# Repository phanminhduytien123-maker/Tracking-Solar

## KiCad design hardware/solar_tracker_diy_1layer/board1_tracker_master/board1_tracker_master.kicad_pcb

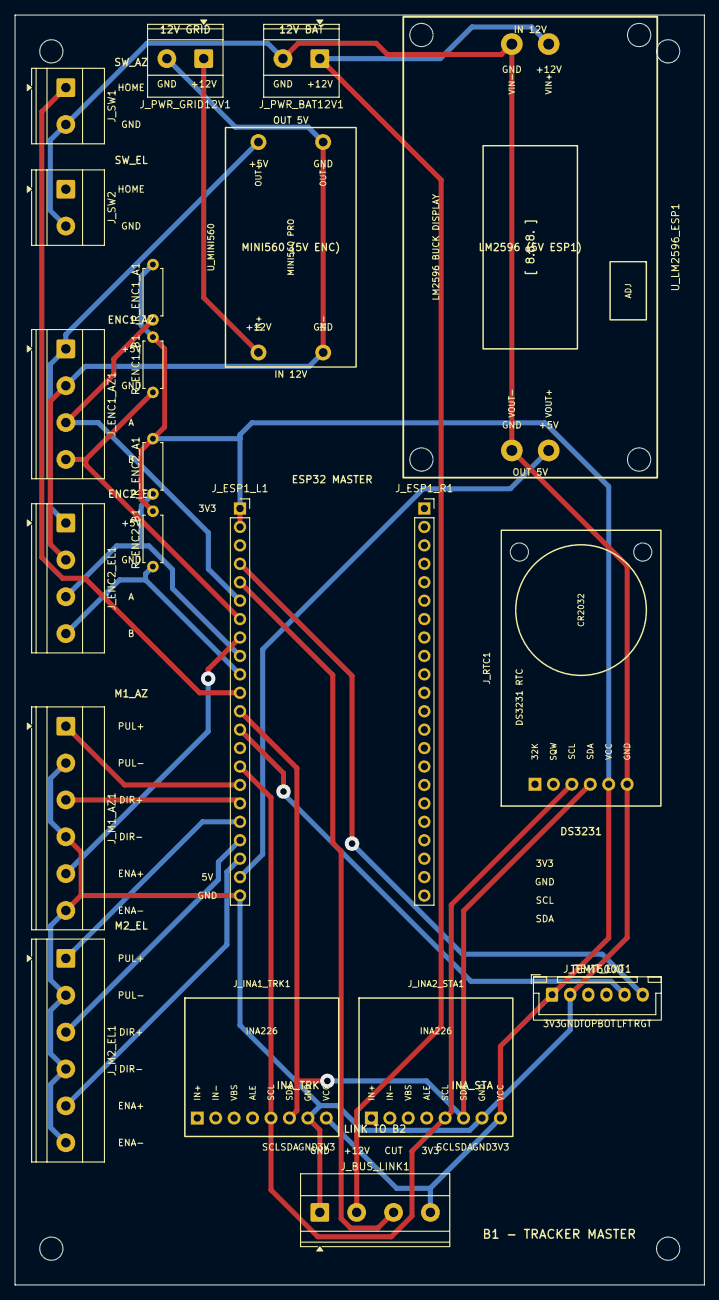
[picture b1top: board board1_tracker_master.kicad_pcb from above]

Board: 2 copper layers, 95.0 x 175.0 mm, 21 parts (0 on the bottom side), 23 nets.

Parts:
J_BUS_LINK1: Bus Lien Bo; TerminalBlock_Phoenix_MKDS-1,5-4-5.08_1x04_P5.08mm_Horizont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
J_ENC1_AZ1: Encoder 1 Az; TerminalBlock_Phoenix_MKDS-1,5-4-5.08_1x04_P5.08mm_Horizont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
J_ENC2_EL1: Encoder 2 El; TerminalBlock_Phoenix_MKDS-1,5-4-5.08_1x04_P5.08mm_Horizont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
J_ESP1_L1: ESP1 J1 Left; PinSocket_1x22_P2.54mm_Vertical
J_ESP1_R1: ESP1 J3 Right; PinSocket_1x22_P2.54mm_Vertical
J_INA1_TRK1: INA226 Trk; INA226_CJMCU226_Module
J_INA2_STA1: INA226 Sta; INA226_CJMCU226_Module
J_M1_AZ1: DM556 #1 Az; TerminalBlock_Phoenix_MKDS-1,5-6-5.08_1x06_P5.08mm_Horizont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
J_M2_EL1: DM556 #2 El; TerminalBlock_Phoenix_MKDS-1,5-6-5.08_1x06_P5.08mm_Horizont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
J_PWR_BAT12V1: 12V Ac Quy; TerminalBlock_Phoenix_MKDS-1,5-2-5.08_1x02_P5.08mm_Horizont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
J_PWR_GRID12V1: 12V To Ong; TerminalBlock_Phoenix_MKDS-1,5-2-5.08_1x02_P5.08mm_Horizont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
J_RTC1: DS3231 RTC; DS3231_RTC_ZS042_Module
J_SW1: Home Azimuth; TerminalBlock_Phoenix_MKDS-1,5-2-5.08_1x02_P5.08mm_Horizont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
J_SW2: Home Elevation; TerminalBlock_Phoenix_MKDS-1,5-2-5.08_1x02_P5.08mm_Horizont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
J_TEMT_EXT1: TEMT6000; JST_XH_B6B-XH-A_1x06_P2.50mm_Vertical
R_ENC1_A1, R_ENC1_B1, R_ENC2_A1, R_ENC2_B1: 6.2k; R_Axial_DIN0207_L6.3mm_D2.5mm_P7.62mm_Horizontal
U_LM2596_ESP1: LM2596 #1; LM2596_Voltmeter_Display_Module
U_MINI560: Mini560 PRO; Mini560_Buck_Module

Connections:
/+3.3V_ESP1: J_BUS_LINK1.4, J_ESP1_L1.1, J_ESP1_L1.2, J_INA1_TRK1.8, J_INA2_STA1.8, J_RTC1.5, J_TEMT_EXT1.1, R_ENC1_A1.2, R_ENC1_B1.2, R_ENC2_A1.2, R_ENC2_B1.2
/+5V_ENC: J_ENC1_AZ1.1, J_ENC2_EL1.1, U_MINI560.3
/+5V_ESP1: J_ESP1_L1.21, U_LM2596_ESP1.3
/+12V_BAT: J_BUS_LINK1.2, J_PWR_BAT12V1.1, U_LM2596_ESP1.1
/+12V_GRID: J_PWR_GRID12V1.1, U_MINI560.1
/ESP1_CUT_ESP2: J_BUS_LINK1.3, J_ESP1_L1.5
/GND: J_BUS_LINK1.1, J_ESP1_L1.22, J_INA1_TRK1.7, J_INA2_STA1.7, J_M1_AZ1.2, J_M1_AZ1.4, J_M1_AZ1.6, J_M2_EL1.2, J_M2_EL1.4, J_M2_EL1.6, J_PWR_BAT12V1.2, J_RTC1.6, J_SW1.2, J_SW2.2, J_TEMT_EXT1.2, U_LM2596_ESP1.2, U_LM2596_ESP1.4
/GND_PWR: J_ENC1_AZ1.2, J_ENC2_EL1.2, J_PWR_GRID12V1.2, U_MINI560.2, U_MINI560.4
/I2C_SCL_1: J_ESP1_L1.15, J_INA1_TRK1.5, J_INA2_STA1.5, J_RTC1.3
/I2C_SDA_1: J_ESP1_L1.12, J_INA1_TRK1.6, J_INA2_STA1.6, J_RTC1.4
/M1_DIR: J_ESP1_L1.17, J_M1_AZ1.3
/M1_ENA: J_ESP1_L1.8, J_M1_AZ1.5
/M1_ENC_A: J_ENC1_AZ1.3, J_ESP1_L1.6, R_ENC1_A1.1
/M1_ENC_B: J_ENC1_AZ1.4, J_ESP1_L1.7, R_ENC1_B1.1
/M1_HOME: J_ESP1_L1.11, J_SW1.1
/M1_PUL: J_ESP1_L1.16, J_M1_AZ1.1
/M2_DIR: J_ESP1_L1.19, J_M2_EL1.3
/M2_ENA: J_ESP1_L1.20, J_M2_EL1.5
/M2_ENC_A: J_ENC2_EL1.3, J_ESP1_L1.9, R_ENC2_A1.1
/M2_ENC_B: J_ENC2_EL1.4, J_ESP1_L1.10, R_ENC2_B1.1
/M2_PUL: J_ESP1_L1.18, J_M2_EL1.1
/TEMT_LFT: J_ESP1_L1.13, J_TEMT_EXT1.5
/TEMT_RGT: J_ESP1_L1.4, J_TEMT_EXT1.6

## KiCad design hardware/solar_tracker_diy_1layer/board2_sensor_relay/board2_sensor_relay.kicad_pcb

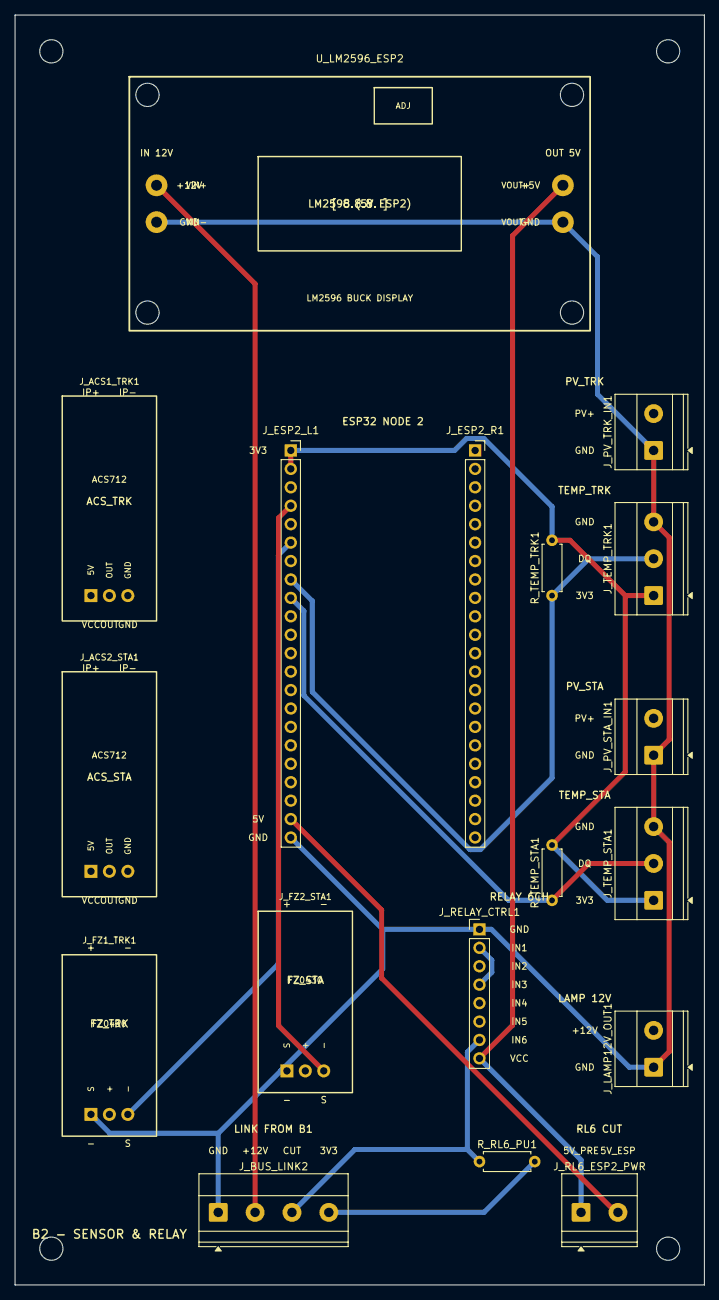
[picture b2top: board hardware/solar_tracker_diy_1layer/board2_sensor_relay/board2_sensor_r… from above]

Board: 2 copper layers, 95.0 x 175.0 mm, 18 parts (0 on the bottom side), 12 nets.

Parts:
J_ACS1_TRK1: ACS712 Trk; ACS712_Current_Sensor_Module
J_ACS2_STA1: ACS712 Sta; ACS712_Current_Sensor_Module
J_BUS_LINK2: Bus Lien Bo; TerminalBlock_Phoenix_MKDS-1,5-4-5.08_1x04_P5.08mm_Horizont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
J_ESP2_L1: ESP2 J1 Left; PinSocket_1x22_P2.54mm_Vertical
J_ESP2_R1: ESP2 J3 Right; PinSocket_1x22_P2.54mm_Vertical
J_FZ1_TRK1: FZ0430 Trk; FZ0430_Voltage_Sensor_Module
J_FZ2_STA1: FZ0430 Sta; FZ0430_Voltage_Sensor_Module
J_LAMP12V_OUT1: Den 12V; TerminalBlock_Phoenix_MKDS-1,5-2-5.08_1x02_P5.08mm_Horizont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
J_PV_STA_IN1: PV Sta; TerminalBlock_Phoenix_MKDS-1,5-2-5.08_1x02_P5.08mm_Horizont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
J_PV_TRK_IN1: PV Trk; TerminalBlock_Phoenix_MKDS-1,5-2-5.08_1x02_P5.08mm_Horizont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
J_RELAY_CTRL1: Relay 6ch Hdr; PinHeader_1x08_P2.54mm_Vertical
J_RL6_ESP2_PWR: Relay 6 Contact; TerminalBlock_Phoenix_MKDS-1,5-2-5.08_1x02_P5.08mm_Horizont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
J_TEMP_STA1: Temp Sta; TerminalBlock_Phoenix_MKDS-1,5-3-5.08_1x03_P5.08mm_Horizont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
J_TEMP_TRK1: Temp Trk; TerminalBlock_Phoenix_MKDS-1,5-3-5.08_1x03_P5.08mm_Horizont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
R_RL6_PU1: 10k Pullup; R_Axial_DIN0207_L6.3mm_D2.5mm_P7.62mm_Horizontal
R_TEMP_STA1: 4.7k; R_Axial_DIN0207_L6.3mm_D2.5mm_P7.62mm_Horizontal
R_TEMP_TRK1: 4.7k; R_Axial_DIN0207_L6.3mm_D2.5mm_P7.62mm_Horizontal
U_LM2596_ESP2: LM2596 #2; LM2596_Voltmeter_Display_Module

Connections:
/+3.3V_ESP1: J_BUS_LINK2.4, R_RL6_PU1.2
/+3.3V_ESP2: J_ESP2_L1.1, J_ESP2_L1.2, J_TEMP_STA1.1, J_TEMP_TRK1.1, R_TEMP_STA1.2, R_TEMP_TRK1.2
/+5V_ESP2: J_ESP2_L1.21, J_RL6_ESP2_PWR.2
/+5V_ESP2_PRE: J_RELAY_CTRL1.8, J_RL6_ESP2_PWR.1, U_LM2596_ESP2.3
/+12V_BAT: J_BUS_LINK2.2, U_LM2596_ESP2.1
/ESP1_CUT_ESP2: J_BUS_LINK2.3, J_RELAY_CTRL1.7, R_RL6_PU1.1
/GND: J_BUS_LINK2.1, J_ESP2_L1.22, J_FZ1_TRK1.1, J_FZ2_STA1.1, J_LAMP12V_OUT1.1, J_PV_STA_IN1.1, J_PV_TRK_IN1.1, J_RELAY_CTRL1.1, J_TEMP_STA1.3, J_TEMP_TRK1.3, U_LM2596_ESP2.2, U_LM2596_ESP2.4
/RL_CUT_38: J_RELAY_CTRL1.2, J_RELAY_CTRL1.4
/TEMP_STA: J_ESP2_L1.9, J_TEMP_STA1.2, R_TEMP_STA1.1
/TEMP_TRK: J_ESP2_L1.8, J_TEMP_TRK1.2, R_TEMP_TRK1.1
/VOC_STA: J_ESP2_L1.4, J_FZ2_STA1.3
/VOC_TRK: J_ESP2_L1.6, J_FZ1_TRK1.3

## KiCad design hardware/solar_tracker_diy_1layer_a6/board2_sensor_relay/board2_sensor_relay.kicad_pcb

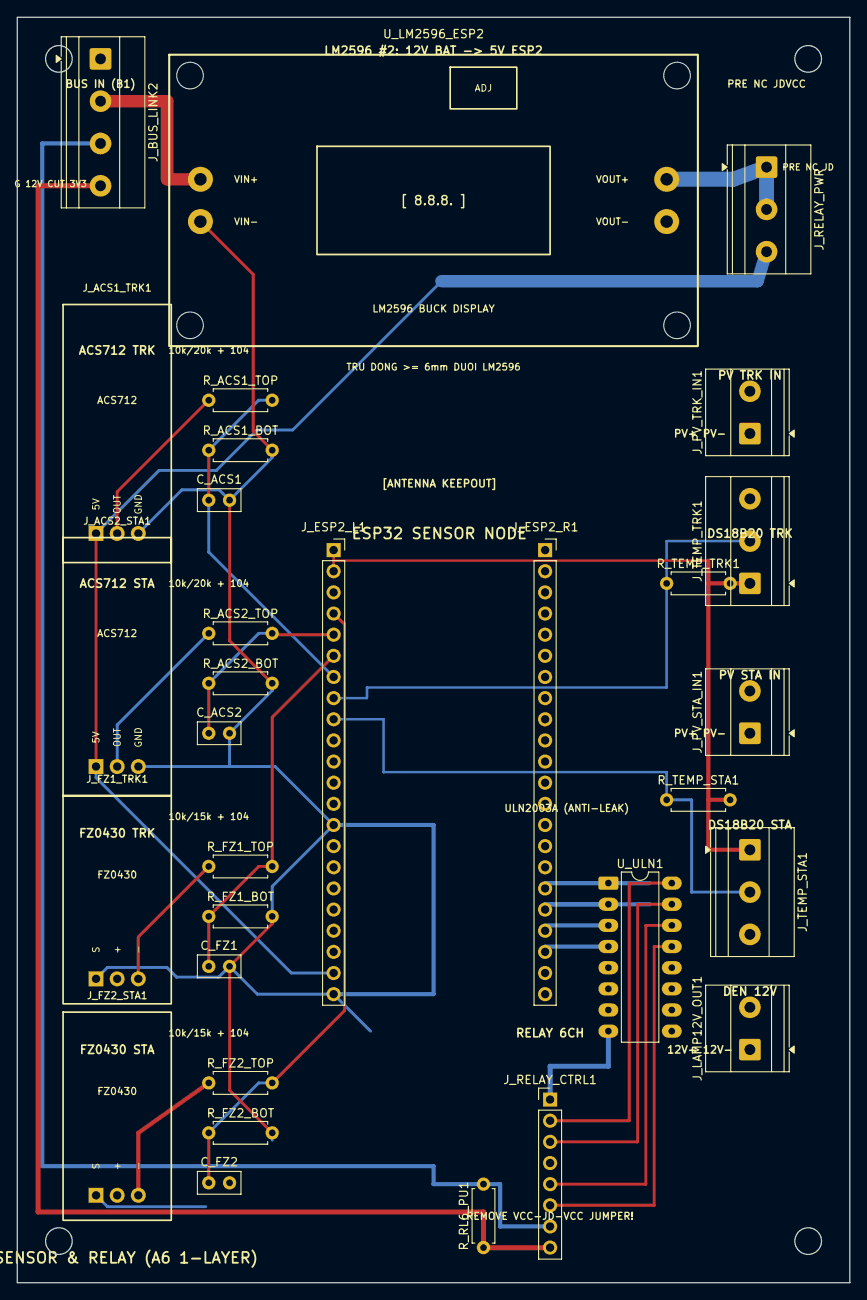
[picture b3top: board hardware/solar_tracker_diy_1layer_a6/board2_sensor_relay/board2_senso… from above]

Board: 2 copper layers, 100.0 x 152.0 mm, 31 parts (0 on the bottom side), 25 nets.

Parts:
C_ACS1, C_ACS2: C_Disc_D5.0mm_W2.5mm_P2.50mm; C_Disc_100nF_P2.5mm
C_FZ1, C_FZ2: C_Disc_D5.0mm_W2.5mm_P2.50mm; C_Disc_100nF_P2.5mm
J_ACS1_TRK1: ACS712 Trk; ACS712_Current_Sensor_Module
J_ACS2_STA1: ACS712 Sta; ACS712_Current_Sensor_Module
J_BUS_LINK2: Bus Lien Bo; TerminalBlock_Phoenix_MKDS-1,5-4-5.08_1x04_P5.08mm_Horizont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
J_ESP2_L1: ESP2 J1 Left; PinSocket_1x22_P2.54mm_Vertical
J_ESP2_R1: ESP2 J3 Right; PinSocket_1x22_P2.54mm_Vertical
J_FZ1_TRK1: FZ0430 Trk; FZ0430_Voltage_Sensor_Module
J_FZ2_STA1: FZ0430 Sta; FZ0430_Voltage_Sensor_Module
J_LAMP12V_OUT1: Den 12V; TerminalBlock_Phoenix_MKDS-1,5-2-5.08_1x02_P5.08mm_Horizont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
J_PV_STA_IN1: PV Sta; TerminalBlock_Phoenix_MKDS-1,5-2-5.08_1x02_P5.08mm_Horizont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
J_PV_TRK_IN1: PV Trk; TerminalBlock_Phoenix_MKDS-1,5-2-5.08_1x02_P5.08mm_Horizont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
J_RELAY_CTRL1: Relay 6ch Hdr; PinHeader_1x08_P2.54mm_Vertical
J_RELAY_PWR: TerminalBlock_Phoenix_MKDS-1,5-3-5.08_1x03_P5.08m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; TerminalBlock_3Pin_P5.08mm
J_TEMP_STA1: Temp Sta; TerminalBlock_Phoenix_MKDS-1,5-3-5.08_1x03_P5.08mm_Horizont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
J_TEMP_TRK1: Temp Trk; TerminalBlock_Phoenix_MKDS-1,5-3-5.08_1x03_P5.08mm_Horizont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
R_ACS1_BOT, R_ACS2_BOT: 20k; R_Axial_DIN0207_L6.3mm_D2.5mm_P7.62mm_Horizontal
R_ACS1_TOP, R_ACS2_TOP: 10k; R_Axial_DIN0207_L6.3mm_D2.5mm_P7.62mm_Horizontal
R_FZ1_BOT, R_FZ2_BOT: 20k; R_Axial_DIN0207_L6.3mm_D2.5mm_P7.62mm_Horizontal
R_FZ1_TOP, R_FZ2_TOP: 10k; R_Axial_DIN0207_L6.3mm_D2.5mm_P7.62mm_Horizontal
R_RL6_PU1: 10k Pullup; R_Axial_DIN0207_L6.3mm_D2.5mm_P7.62mm_Horizontal
R_TEMP_STA1: 4.7k; R_Axial_DIN0207_L6.3mm_D2.5mm_P7.62mm_Horizontal
R_TEMP_TRK1: 4.7k; R_Axial_DIN0207_L6.3mm_D2.5mm_P7.62mm_Horizontal
U_LM2596_ESP2: LM2596 #2; LM2596_Voltmeter_Display_Module
U_ULN1: DIP-16_W7.62mm_LongPads; ULN2003A_DIP16

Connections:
/+3.3V_ESP1: J_BUS_LINK2.4, J_RELAY_CTRL1.8, R_RL6_PU1.1
/+3.3V_ESP2: J_ESP2_L1.1, J_ESP2_L1.2, J_TEMP_STA1.1, J_TEMP_TRK1.1, R_TEMP_STA1.2, R_TEMP_TRK1.2
/+5V_ESP2: J_ACS1_TRK1.1, J_ACS2_STA1.1, J_ESP2_L1.21, J_RELAY_PWR.3
/+5V_ESP2_PRE: J_RELAY_PWR.1, J_RELAY_PWR.2, U_LM2596_ESP2.3
/+12V_BAT: J_BUS_LINK2.2, U_LM2596_ESP2.1
/ESP1_CUT_ESP2: J_BUS_LINK2.3, J_RELAY_CTRL1.7, R_RL6_PU1.2
/GND: C_ACS1.2, C_ACS2.2, C_FZ1.2, C_FZ2.2, J_ACS1_TRK1.3, J_ACS2_STA1.3, J_BUS_LINK2.1, J_ESP2_L1.14, J_ESP2_L1.22, J_FZ1_TRK1.1, J_FZ2_STA1.1, J_LAMP12V_OUT1.1, J_PV_STA_IN1.1, J_PV_TRK_IN1.1, J_RELAY_CTRL1.1, J_TEMP_STA1.3, J_TEMP_TRK1.3, R_ACS1_BOT.2, R_ACS2_BOT.2, R_FZ1_BOT.2, R_FZ2_BOT.2, U_LM2596_ESP2.2, U_LM2596_ESP2.4, U_ULN1.8
/ISC_STA: C_ACS2.1, J_ESP2_L1.5, R_ACS2_BOT.1, R_ACS2_TOP.2
/ISC_TRK: C_ACS1.1, J_ESP2_L1.7, R_ACS1_BOT.1, R_ACS1_TOP.2
/RAW_ISC_STA: J_ACS2_STA1.2, R_ACS2_TOP.1
/RAW_ISC_TRK: J_ACS1_TRK1.2, R_ACS1_TOP.1
/RAW_VOC_STA: J_FZ2_STA1.3, R_FZ2_TOP.1
/RAW_VOC_TRK: J_FZ1_TRK1.3, R_FZ1_TOP.1
/RL_B_ISC: J_ESP2_R1.18, U_ULN1.2
/RL_CUT_38: J_ESP2_R1.17, U_ULN1.1
/RL_DRV_IN1: J_RELAY_CTRL1.2, U_ULN1.16
/RL_DRV_IN2: J_RELAY_CTRL1.3, U_ULN1.15
/RL_DRV_IN4: J_RELAY_CTRL1.5, U_ULN1.14
/RL_DRV_IN5: J_RELAY_CTRL1.6, U_ULN1.13
/RL_D_ISC: J_ESP2_R1.19, U_ULN1.3
/RL_E_LAMP: J_ESP2_R1.20, U_ULN1.4
/TEMP_STA: J_ESP2_L1.9, J_TEMP_STA1.2, R_TEMP_STA1.1
/TEMP_TRK: J_ESP2_L1.8, J_TEMP_TRK1.2, R_TEMP_TRK1.1
/VOC_STA: C_FZ2.1, J_ESP2_L1.4, R_FZ2_BOT.1, R_FZ2_TOP.2
/VOC_TRK: C_FZ1.1, J_ESP2_L1.6, R_FZ1_BOT.1, R_FZ1_TOP.2

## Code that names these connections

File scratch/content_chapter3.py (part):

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                ["ESP32-S3 #1 (Master Tracker)", "I2C Bus (RTC DS3231 + INA226)", "GPIO 8 (SDA) / GPIO 9 (SCL)", "Giao tiếp I2C 400kHz, có timeout chống treo"],
                ["ESP32-S3 #1 (Master Tracker)", "Ngắt 1Hz từ RTC DS3231", "GPIO 47 (SQW/INT)", "Ngắt cứng sườn xuống đánh thức chu trình đo"],
                ["ESP32-S3 #1 (Master Tracker)", "Cảm biến quang TEMT6000 4 hướng", "GPIO 1, 2, 3, 4 (ADC1)", "Top=1, Bot=2, Left=3, Right=4 (Tránh xung đột Wi-Fi)"],
                ["ESP32-S3 #1 (Master Tracker)", "Relay K6 (Cắt nguồn đêm ESP2)", "GPIO 5 (ESP1_CUT_ESP2)", "Ngắt nguồn LM2596 #2 vào ban đêm để tiết kiệm điện"],
                ["ESP32-S3 #2 (Voc/Isc Node)", "Relay K1/K2 (Cắt tải đo Voc)", "GPIO 38 (RL_CUT_38)", "Ngắt tiếp điểm tải để đo điện áp hở mạch Voc"],
                ["ESP32-S3 #2 (Voc/Isc Node)", "Relay K3 (Nối tắt đo Isc Trk)", "GPIO 41 (RL_B_ISC)", "Nối tắt tạm thời tấm Tracking qua ACS712"],
                ["ESP32-S3 #2 (Voc/Isc Node)", "Relay K4 (Nối tắt đo Isc Sta)", "GPIO 39 (RL_D_ISC)", "Nối tắt tạm thời tấm Static qua ACS712"],
                ["ESP32-S3 #2 (Voc/Isc Node)", "Relay K5 (Tải xả đèn đêm 12V)", "GPIO 42 (RL_E_LAMP)", "Đóng nối tải đèn sợi đốt 12V xả ắc quy ban đêm"],
                ["ESP32-S3 #2 (Voc/Isc Node)", "Đo áp Voc (Tấm Tracker / Static)", "GPIO 4, GPIO 5 (ADC1)", "Mạch cầu phân áp FZ0430 tỉ lệ 5:1"],
                ["ESP32-S3 #2 (Voc/Isc Node)", "Đo dòng Isc (Tấm Tracker / Static)", "GPIO 6, GPIO 7 (ADC1)", "Cảm biến dòng Hall tuyến tính ACS712-05B"],
                ["ESP32-S3 #2 (Voc/Isc Node)", "Nhiệt độ DS18B20 Trk / Sta", "GPIO 15, GPIO 16", "2 kênh 1-Wire độc lập, điện trở kéo lên 4.7 kΩ"]
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
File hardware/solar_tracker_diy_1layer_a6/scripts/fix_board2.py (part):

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        b.Add(seg)

    # Right outputs escaping right into clear corridor (x in [90, 93]) then down on B.Cu
    # Pin 16: /RL_DRV_IN1 at (88.62, 114.00) -> J_RELAY_CTRL1 pad 2 (74.00, 142.54)
    # Pin 15: /RL_DRV_IN2 at (88.62, 116.54) -> J_RELAY_CTRL1 pad 3 (74.00, 145.08)
    # Pin 14: /RL_DRV_IN4 at (88.62, 119.08) -> J_RELAY_CTRL1 pad 5 (74.00, 150.16)
    # Pin 13: /RL_DRV_IN5 at (88.62, 121.62) -> J_RELAY_CTRL1 pad 6 (74.00, 152.70)
    out_routes = [
        ((88.62, 114.00), (93.50, 114.00), (93.50, 136.00), (74.00, 142.54), net_in1),
        ((88.62, 116.54), (92.00, 116.54), (92.00, 138.00), (74.00, 145.08), net_in2),
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
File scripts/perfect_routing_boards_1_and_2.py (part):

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add_track(b1, net_12v_bat, 59.08, 158.0, 59.08, 152.0, pcbnew.F_Cu, 1.5)

# B. Route Encoder signals:
# M1_ENC_A: Terminal (17, 58.16) -> R_ENC1_A1 (32, 58) -> ESP1 pin 7 (42, 90.68)
add_track(b1, net_m1_a, 17.0, 58.16, 32.0, 58.0, pcbnew.B_Cu, 0.4)
add_track(b1, net_m1_a, 32.0, 58.0, 38.0, 58.0, pcbnew.B_Cu, 0.4)
add_track(b1, net_m1_a, 38.0, 58.0, 38.0, 90.68, pcbnew.B_Cu, 0.4)
add_track(b1, net_m1_a, 38.0, 90.68, 42.0, 90.68, pcbnew.B_Cu, 0.4)

# M1_ENC_B: Terminal (17, 63.24) -> R_ENC1_B1 (32, 62) -> ESP1 pin 8 (42, 93.22)
add_track(b1, net_m1_b, 17.0, 63.24, 28.0, 63.24, pcbnew.B_Cu, 0.4)
add_track(b1, net_m1_b, 28.0, 63.24, 28.0, 62.0, pcbnew.B_Cu, 0.4)
add_track(b1, net_m1_b, 28.0, 62.0, 32.0, 62.0, pcbnew.B_Cu, 0.4)
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add_track(b1, net_m1_b, 36.5, 62.0, 36.5, 93.22, pcbnew.B_Cu, 0.4)
add_track(b1, net_m1_b, 36.5, 93.22, 42.0, 93.22, pcbnew.B_Cu, 0.4)

# M2_ENC_A: Terminal (17, 82.16) -> R_ENC2_A1 (32, 66) -> ESP1 pin 10 (42, 98.30)
# Use vias for F.Cu jumper over +5V_ENC at y=72
add_track(b1, net_m2_a, 17.0, 82.16, 26.0, 82.16, pcbnew.B_Cu, 0.4)
add_via(b1, net_m2_a, 26.0, 82.16)
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add_track(b1, net_m2_a, 35.0, 66.0, 35.0, 98.30, pcbnew.B_Cu, 0.4)
add_track(b1, net_m2_a, 35.0, 98.30, 42.0, 98.30, pcbnew.B_Cu, 0.4)

# M2_ENC_B: Terminal (17, 87.24) -> R_ENC2_B1 (32, 70) -> ESP1 pin 11 (42, 100.84)
add_track(b1, net_m2_b, 17.0, 87.24, 24.0, 87.24, pcbnew.B_Cu, 0.4)
add_via(b1, net_m2_b, 24.0, 87.24)
add_track(b1, net_m2_b, 24.0, 87.24, 24.0, 70.0, pcbnew.F_Cu, 0.4)
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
